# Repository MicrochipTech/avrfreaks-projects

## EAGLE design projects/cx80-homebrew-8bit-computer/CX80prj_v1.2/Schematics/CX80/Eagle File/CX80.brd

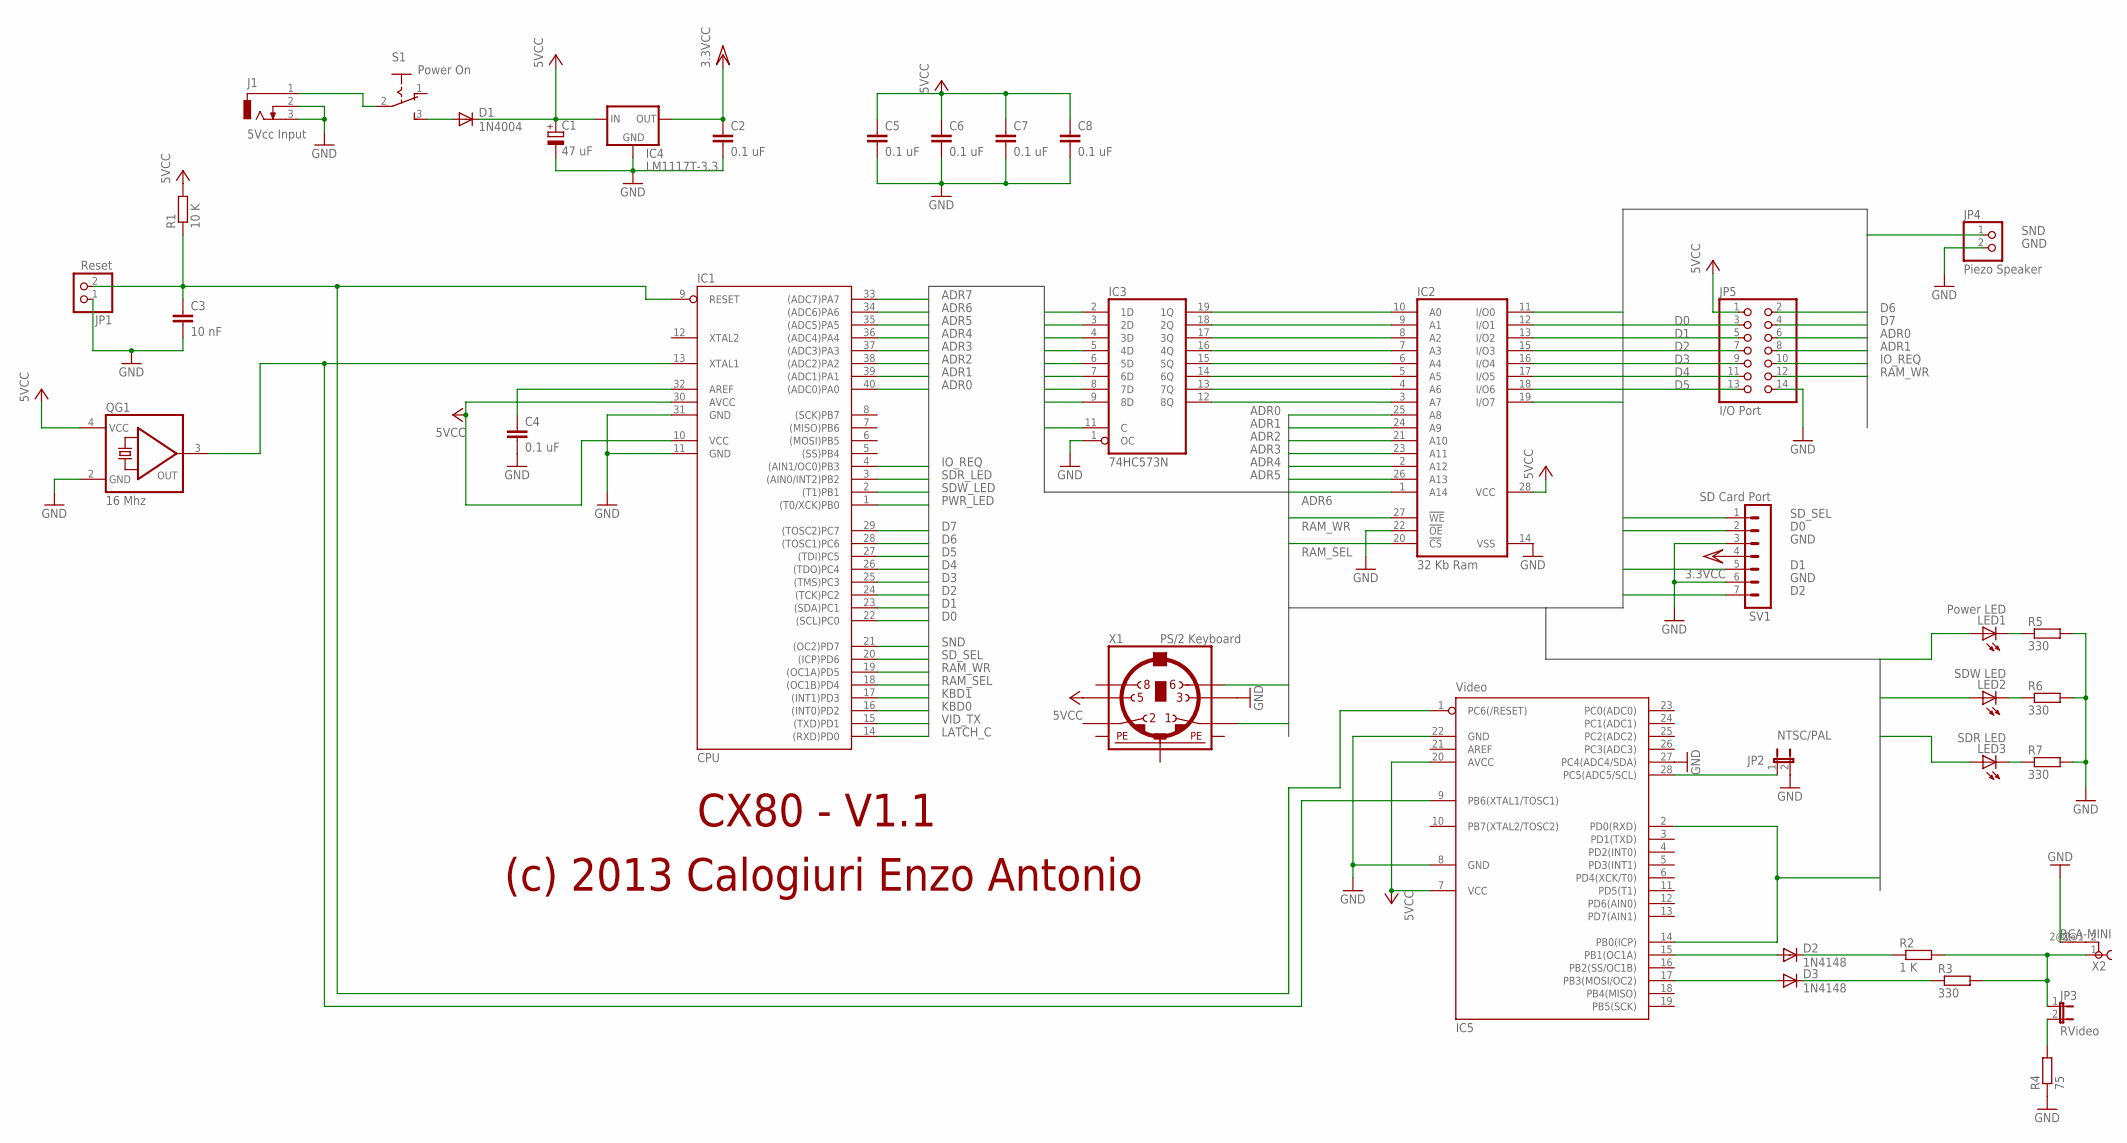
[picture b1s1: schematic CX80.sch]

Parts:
C1: 47 uF; E2,5-5
C2, C4, C5, C6, C7, C8: 0.1 uF; C050-030X075
C3: 10 nF; C050-030X075
D1: 1N4004; DO41-10
D2, D3: 1N4148; DO35-10
IC1: CPU; DIL40
IC2: 32 Kb Ram; DIL28-3
IC3: 74HC573N; DIL20
IC4: LM1117T-3.3; TO220
IC5: Video; DIL28-3
J1: 5Vcc Input; DCJ0303
JP1: Reset; 1X02
JP2: NTSC/PAL; JP1
JP3: RVideo; JP1
JP4: Piezo Speaker; 1X02
JP5: I/O Port; 2X07
LED1: Power LED; LED3MM
LED2: SDW LED; LED3MM
LED3: SDR LED; LED3MM
QG1: 16 Mhz; DIL08-4
R1: 10 K; 0207/10
R2: 1 K; 0207/10
R3, R5, R6, R7: 330; 0207/10
R4: 75; 0207/10
S1: Power On; 255SB
SV1: SD Card Port; MA07-1
X1: PS/2 Keyboard; M_DIN6
X2: RCA-MINI

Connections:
ADR0: IC1.40 ((ADC0)PA0), IC2.25 (A8), IC3.2 (1D), JP5.6
ADR1: IC1.39 ((ADC1)PA1), IC2.24 (A9), IC3.3 (2D), JP5.8
ADR2: IC1.38 ((ADC2)PA2), IC2.21 (A10), IC3.4 (3D)
ADR3: IC1.37 ((ADC3)PA3), IC2.23 (A11), IC3.5 (4D)
ADR4: IC1.36 ((ADC4)PA4), IC2.2 (A12), IC3.6 (5D)
ADR5: IC1.35 ((ADC5)PA5), IC2.26 (A13), IC3.7 (6D)
ADR6: IC1.34 ((ADC6)PA6), IC2.1 (A14), IC3.8 (7D)
ADR7: IC1.33 ((ADC7)PA7), IC3.9 (8D)
D0: IC1.22 ((SCL)PC0), IC2.11 (I/O0), JP5.3, SV1.2
D1: IC1.23 ((SDA)PC1), IC2.12 (I/O1), JP5.5, SV1.5
D2: IC1.24 ((TCK)PC2), IC2.13 (I/O2), JP5.7, SV1.7
D3: IC1.25 ((TMS)PC3), IC2.15 (I/O3), JP5.9
D4: IC1.26 ((TDO)PC4), IC2.16 (I/O4), JP5.11
D5: IC1.27 ((TDI)PC5), IC2.17 (I/O5), JP5.13
D6: IC1.28 ((TOSC1)PC6), IC2.18 (I/O6), JP5.2
D7: IC1.29 ((TOSC2)PC7), IC2.19 (I/O7), JP5.4
GND: C1.-, C2.2, C3.2, C4.2, C5.2, C6.2, C7.2, C8.2, IC1.11 (GND), IC1.31 (GND), IC2.14 (VSS), IC2.22 (!OE), IC3.1 (OC), IC3.10 (GND), IC4.1 (GND), IC5.8 (GND), IC5.22 (GND), IC5.27 (PC4(ADC4/SDA)), J1.2, J1.3, JP1.1, JP2.2, JP4.2, JP5.14, QG1.2 (GND), R4.1, R5.2, R6.2, R7.2, SV1.3, SV1.6, X1.3, X2.2@2 (4)
IO_REQ: IC1.4 ((AIN1/OC0)PB3), JP5.10
KBD0: IC1.16 ((INT0)PD2), X1.6
KBD1: IC1.17 ((INT1)PD3), X1.1
LATCH_C: IC1.14 ((RXD)PD0), IC3.11 (C)
unnamed: D1.A, S1.3 (S)
unnamed: IC2.10 (A0), IC3.19 (1Q)
unnamed: C3.1, IC1.9 (RESET), IC5.1 (PC6(/RESET)), JP1.2, R1.1
unnamed: IC2.9 (A1), IC3.18 (2Q)
unnamed: IC1.13 (XTAL1), IC5.9 (PB6(XTAL1/TOSC1)), QG1.3 (OUT)
unnamed: C4.1, IC1.32 (AREF)
unnamed: IC2.8 (A2), IC3.17 (3Q)
unnamed: IC2.7 (A3), IC3.16 (4Q)
unnamed: IC2.6 (A4), IC3.15 (5Q)
unnamed: IC2.5 (A5), IC3.14 (6Q)
unnamed: IC2.4 (A6), IC3.13 (7Q)
unnamed: IC2.3 (A7), IC3.12 (8Q)
unnamed: IC5.28 (PC5(ADC5/SCL)), JP2.1
unnamed: D2.A, IC5.15 (PB1(OC1A))
unnamed: D2.C, R2.1
unnamed: D3.A, IC5.17 (PB3(MOSI/OC2))
unnamed: D3.C, R3.1
unnamed: JP3.1, R2.2, R3.2, X2.1
unnamed: JP3.2, R4.2
unnamed: J1.1, S1.2
unnamed: LED1.K (C), R5.1
unnamed: LED2.K (C), R6.1
unnamed: LED3.K (C), R7.1
PE1: X1.SH1 (PE1)
PE2: X1.SH2 (PE2)
PE3: X1.SH3 (PE3)
PWR_LED: IC1.1 ((T0/XCK)PB0), LED1.A
RAM_SEL: IC1.18 ((OC1B)PD4), IC2.20 (!CS)
RAM_WR: IC1.19 ((OC1A)PD5), IC2.27 (!WE), JP5.12
SDR_LED: IC1.3 ((AIN0/INT2)PB2), LED3.A
SDW_LED: IC1.2 ((T1)PB1), LED2.A
SD_SEL: IC1.20 ((ICP)PD6), SV1.1
SND: IC1.21 ((OC2)PD7), JP4.1
VCC: C1.+, C5.1, C6.1, C7.1, C8.1, D1.C, IC1.10 (VCC), IC1.30 (AVCC), IC2.28 (VCC), IC3.20 (VCC), IC4.3 (IN), IC5.7 (VCC), IC5.20 (AVCC), JP5.1, QG1.4 (VCC), R1.2, X1.5
VCC/2: C2.1, IC4.2 (OUT), SV1.4
VID_TX: IC1.15 ((TXD)PD1), IC5.2 (PD0(RXD)), IC5.14 (PB0(ICP))

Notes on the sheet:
CX80 - V1.1
(c) 2013 Calogiuri Enzo Antonio

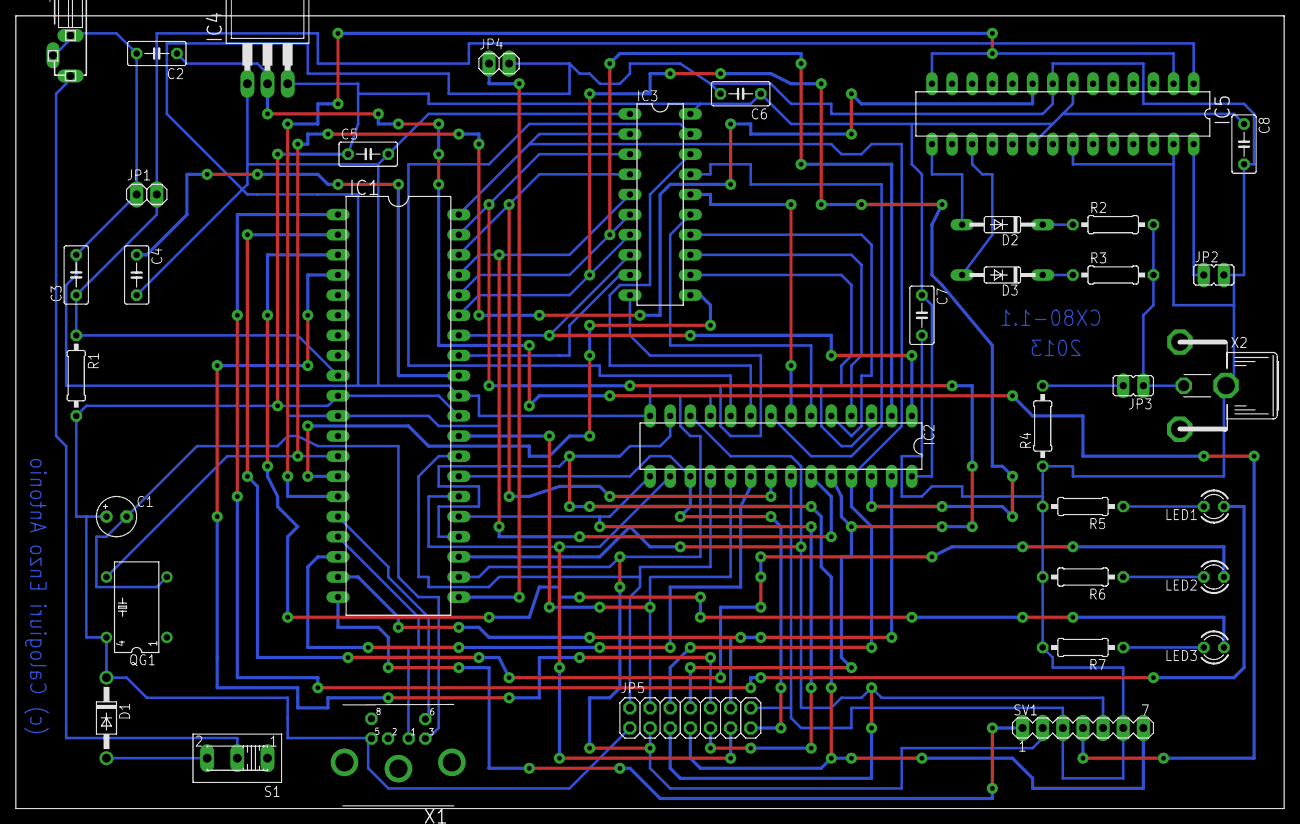
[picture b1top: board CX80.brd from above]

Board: 2 copper layers, 160.0 x 100.0 mm, 37 parts (0 on the bottom side), 54 nets.

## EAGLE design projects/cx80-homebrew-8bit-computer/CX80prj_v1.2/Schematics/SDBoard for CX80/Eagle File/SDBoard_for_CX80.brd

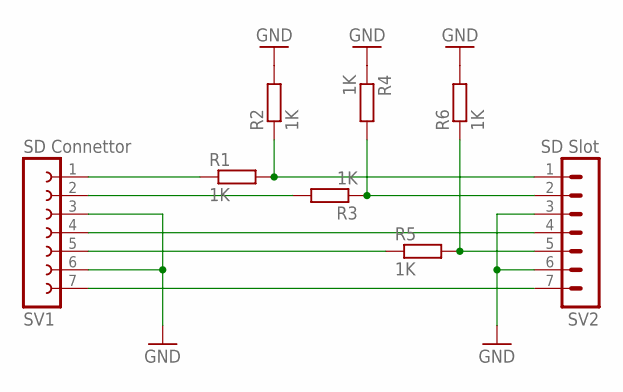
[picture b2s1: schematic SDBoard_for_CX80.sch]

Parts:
R1, R2, R3, R4, R5, R6: 1K; 0207/12
SV1: SD Connettor; FE07
SV2: SD Slot; MA07-1

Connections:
GND: R2.2, R4.1, R6.2, SV1.3, SV1.6, SV2.3, SV2.6
unnamed: R1.1, SV1.1
unnamed: R1.2, R2.1, SV2.1
unnamed: R3.2, SV1.2
unnamed: R3.1, R4.2, SV2.2
unnamed: R5.1, SV1.5
unnamed: R5.2, R6.1, SV2.5
unnamed: SV1.4, SV2.4
unnamed: SV1.7, SV2.7

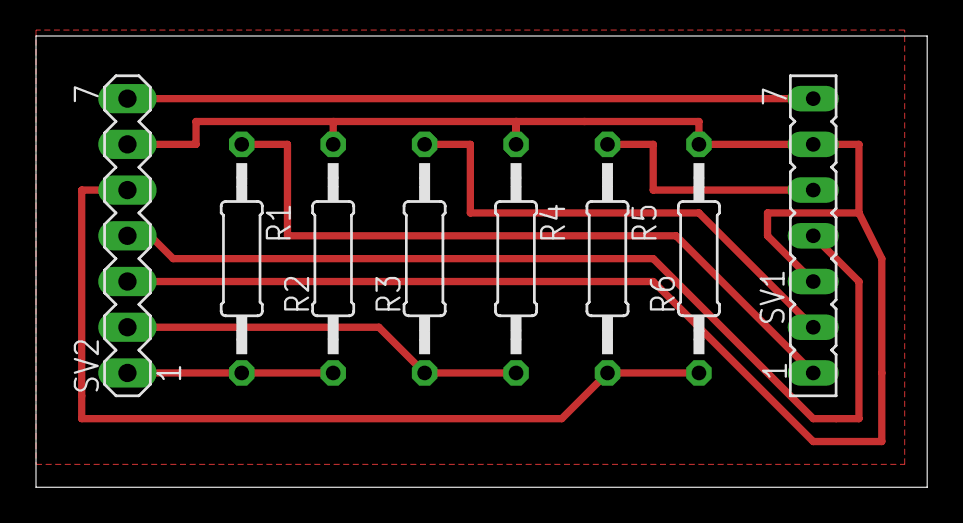
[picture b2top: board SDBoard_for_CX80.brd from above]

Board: 2 copper layers, 49.5 x 25.1 mm, 8 parts (0 on the bottom side), 9 nets.

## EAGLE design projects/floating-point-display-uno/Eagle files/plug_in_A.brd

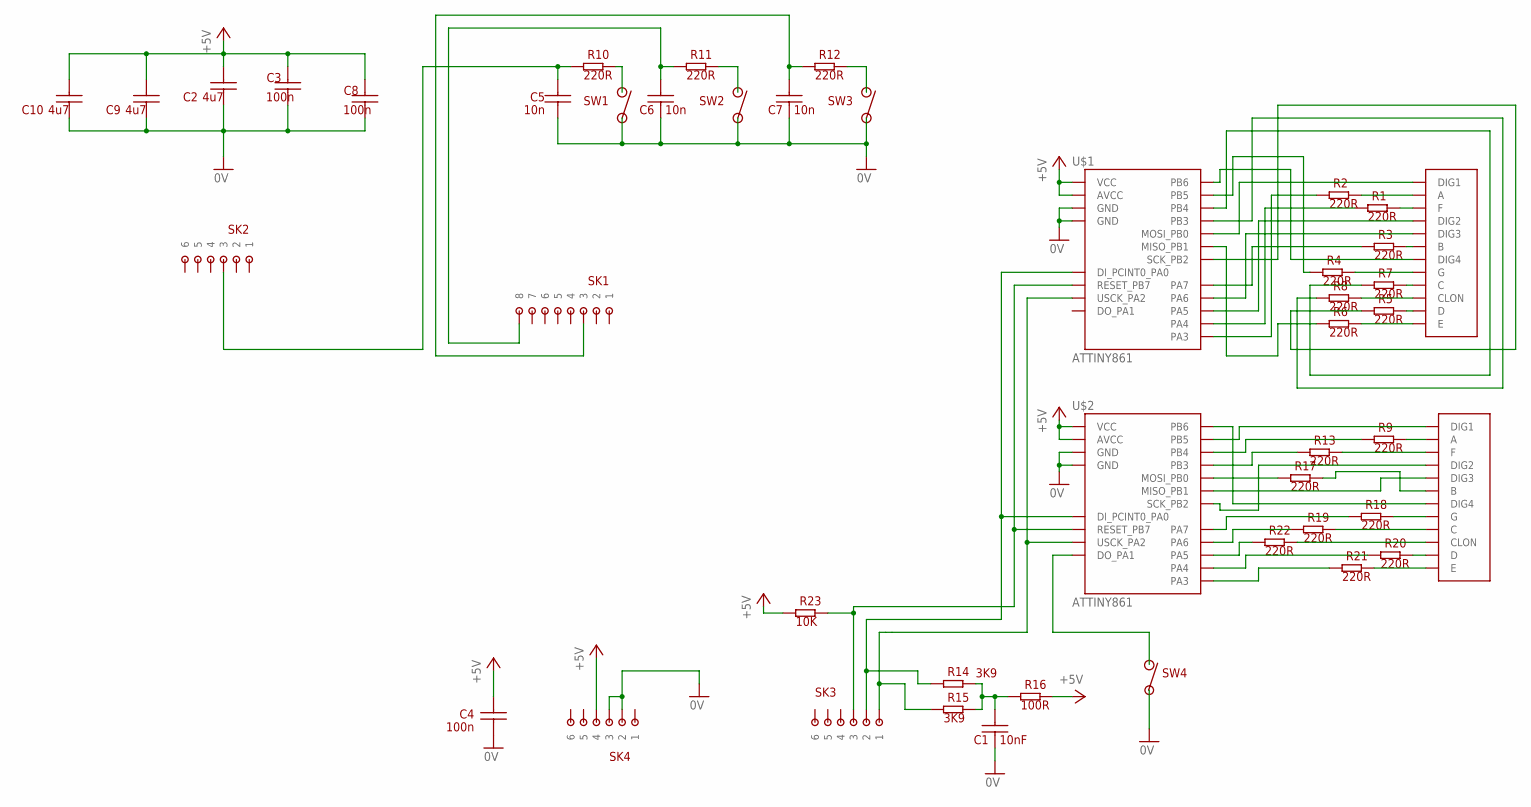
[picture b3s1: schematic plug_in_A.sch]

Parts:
C1: 10nF; 1206
C2, C9, C10: 4u7; 1206
C3, C4, C8: 100n; 1206
C5, C6, C7: 10n; 1206
R1, R2, R3, R4, R5, R6, R7, R8, R9, R10, R11, R12, R13, R17, R18, R19, R20, R21, R22: 220R; 1206
R14, R15: 3K9; 1206
R16: 100R; 1206
R23: 10K; 1206
SK1: 8_WAY_HEADER
SK2, SK3, SK4: 6_WAY_HEADER
SW1, SW2, SW3: BP_TH_NO; PB_NO_TH
SW4: PUSH_BUTTON_NO_SM
U$1, U$2: ATTINY861; DIL20
U$3, U$4: DISPLAY

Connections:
0V: C1.P$1, C2.P$1, C3.P$1, C4.P$1, C5.P$1, C6.P$1, C7.P$1, C8.P$1, C9.P$1, C10.P$1, SK4.P$2 (2), SK4.P$3 (3), SW1.P$2, SW2.P$2, SW3.P$2, SW4.P$2, U$1.6 (GND), U$1.16 (GND), U$2.6 (GND), U$2.16 (GND)
+5V: C2.P$2, C3.P$2, C4.P$2, C8.P$2, C9.P$2, C10.P$2, R16.P$2 (2), R23.P$1 (1), SK4.P$4 (4), U$1.5 (VCC), U$1.15 (AVCC), U$2.5 (VCC), U$2.15 (AVCC)
unnamed: SW4.P$1, U$2.19 (DO_PA1)
unnamed: U$1.1 (MOSI_PB0), U$3.P$12 (DIG1)
unnamed: U$1.12 (PA6), U$3.P$8 (DIG3)
unnamed: U$1.13 (PA5), U$3.P$9 (DIG2)
unnamed: R2.P$1 (1), U$1.17 (PA3)
unnamed: R23.P$2 (2), SK3.P$3 (3), U$1.10 (RESET_PB7), U$2.10 (RESET_PB7)
unnamed: R20.P$1 (1), U$2.14 (PA4)
unnamed: R6.P$1 (1), U$1.2 (MISO_PB1)
unnamed: U$1.9 (PB6), U$3.P$6 (DIG4)
unnamed: R14.P$1 (1), SK3.P$2 (2), U$1.20 (DI_PCINT0_PA0), U$2.20 (DI_PCINT0_PA0)
unnamed: R15.P$1 (1), SK3.P$1 (1), U$1.18 (USCK_PA2), U$2.18 (USCK_PA2)
unnamed: R10.P$2 (2), SW1.P$1
unnamed: R11.P$2 (2), SW2.P$1
unnamed: R12.P$2 (2), SW3.P$1
unnamed: C7.P$2, R12.P$1 (1), SK1.P$3 (3)
unnamed: R4.P$1 (1), U$1.8 (PB5)
unnamed: C5.P$2, R10.P$1 (1), SK2.P$3 (3)
unnamed: C6.P$2, R11.P$1 (1), SK1.P$8 (8)
unnamed: C1.P$2, R14.P$2 (2), R15.P$2 (2), R16.P$1 (1)
unnamed: R8.P$1 (1), U$1.4 (PB3)
unnamed: R7.P$1 (1), U$1.7 (PB4)
unnamed: R5.P$1 (1), U$1.3 (SCK_PB2)
unnamed: R1.P$1 (1), U$1.14 (PA4)
unnamed: R3.P$1 (1), U$1.11 (PA7)
unnamed: U$2.9 (PB6), U$4.P$6 (DIG4)
unnamed: R4.P$2 (2), U$3.P$5 (G)
unnamed: R18.P$1 (1), U$2.11 (PA7)
unnamed: R19.P$1 (1), U$2.12 (PA6)
unnamed: R22.P$1 (1), U$2.13 (PA5)
unnamed: R2.P$2 (2), U$3.P$11 (A)
unnamed: R21.P$1 (1), U$2.17 (PA3)
unnamed: U$2.8 (PB5), U$4.P$12 (DIG1)
unnamed: R9.P$1 (1), U$2.7 (PB4)
unnamed: R13.P$1 (1), U$2.4 (PB3)
unnamed: U$2.3 (SCK_PB2), U$4.P$9 (DIG2)
unnamed: U$2.2 (MISO_PB1), U$4.P$8 (DIG3)
unnamed: R17.P$2 (2), U$4.P$7 (B)
unnamed: R3.P$2 (2), U$3.P$7 (B)
unnamed: R1.P$2 (2), U$3.P$10 (F)
unnamed: R7.P$2 (2), U$3.P$4 (C)
unnamed: R5.P$2 (2), U$3.P$2 (D)
unnamed: R6.P$2 (2), U$3.P$1 (E)
unnamed: R8.P$2 (2), U$3.P$3 (CLON)
unnamed: R17.P$1 (1), U$2.1 (MOSI_PB0)
unnamed: R9.P$2 (2), U$4.P$11 (A)
unnamed: R13.P$2 (2), U$4.P$10 (F)
unnamed: R18.P$2 (2), U$4.P$5 (G)
unnamed: R19.P$2 (2), U$4.P$4 (C)
unnamed: R20.P$2 (2), U$4.P$2 (D)
unnamed: R21.P$2 (2), U$4.P$1 (E)
unnamed: R22.P$2 (2), U$4.P$3 (CLON)

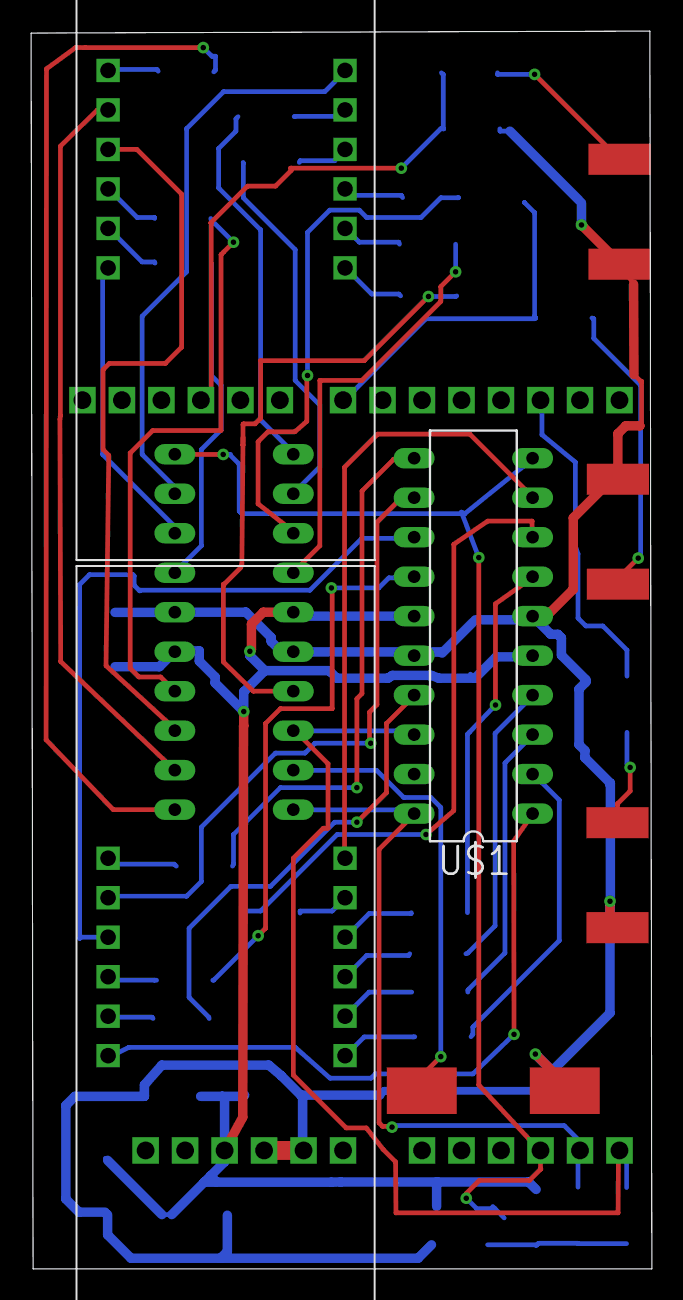
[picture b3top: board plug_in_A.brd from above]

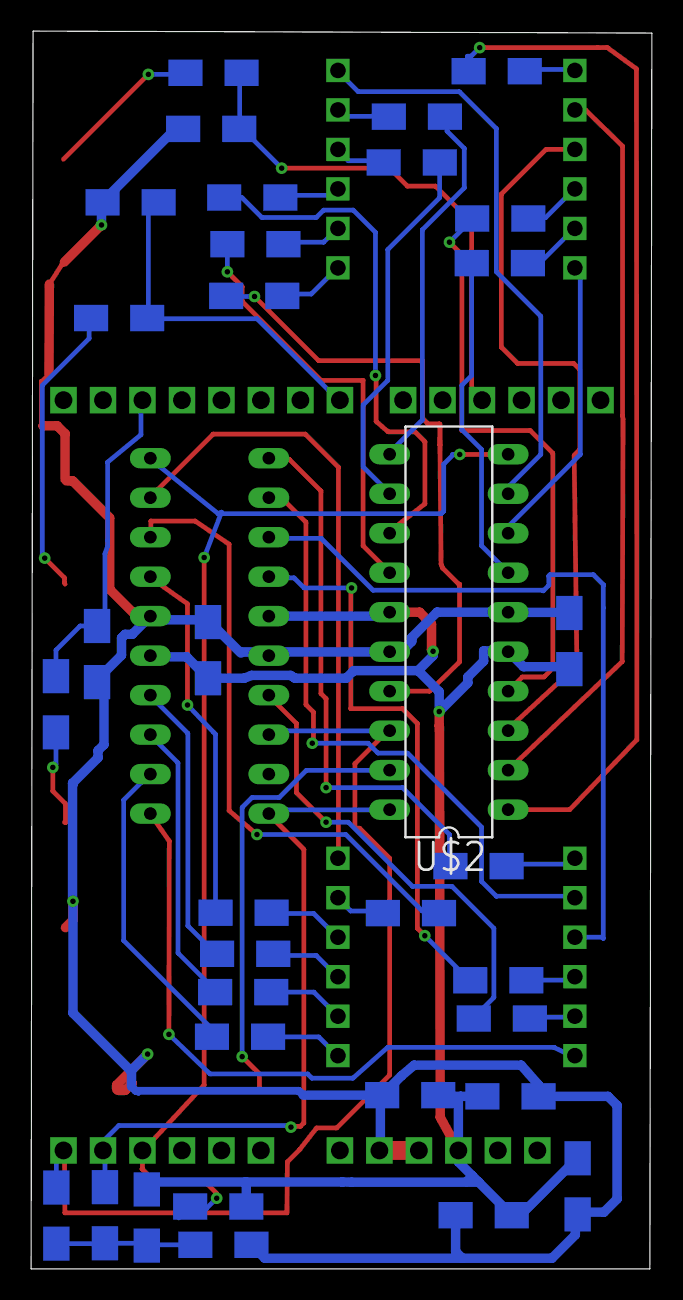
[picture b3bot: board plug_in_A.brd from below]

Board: 2 copper layers, 39.9 x 79.6 mm, 45 parts (34 on the bottom side), 53 nets.
